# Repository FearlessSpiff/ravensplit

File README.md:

# ravensplit

(MX) Low profile split version of the raveniung

### First time setup

* Install ergogen: `npm install -g ergogen`
* Get footprints from ceoloide: `git clone https://github.com/ceoloide/ergogen-footprints ergogen/footprints/ceoloide`
* For case build install `npm install -g @jscad/cli`

## v0.1 for Cirque Trackpad

### Build

```bash
cd ergogen
cp config-v0.1.yaml config.yaml
ergogen .
```

or for building including the left case:

```bash
ergogen . && npx @jscad/cli@1 output/cases/LeftCase.jscad -of stla && npx @jscad/cli@1 output/cases/RightCase.jscad -of stla
```

### Notes

* mirror right case and cirque holder!

## v0.2 for Azoteq TPS65 touchpad

### Build

```bash
cd ergogen
cp config-v0.2.yaml config.yaml
ergogen .
```

or for building including the left case:

```bash
ergogen . && npx @jscad/cli@1 output/cases/LeftCase.jscad -of stla
```

### Notes

* mirror right case and cirque holder!
For 3d printed  case:
* top-foam-plate: 1mm thick, cut 15mm/s 90%
* bottom-foam-plate: 3mm thick, cut 12mm/s 90% 2 passes
* touchpad-overlay-tps43 sticker: Tenstickers brand vinyl, cut 10mm/s 80% power on a 10W laser
* touchpad-overlay-tps65 sticker: Tenstickers brand vinyl, cut 10mm/s 80% power on a 10W laser

### TODO

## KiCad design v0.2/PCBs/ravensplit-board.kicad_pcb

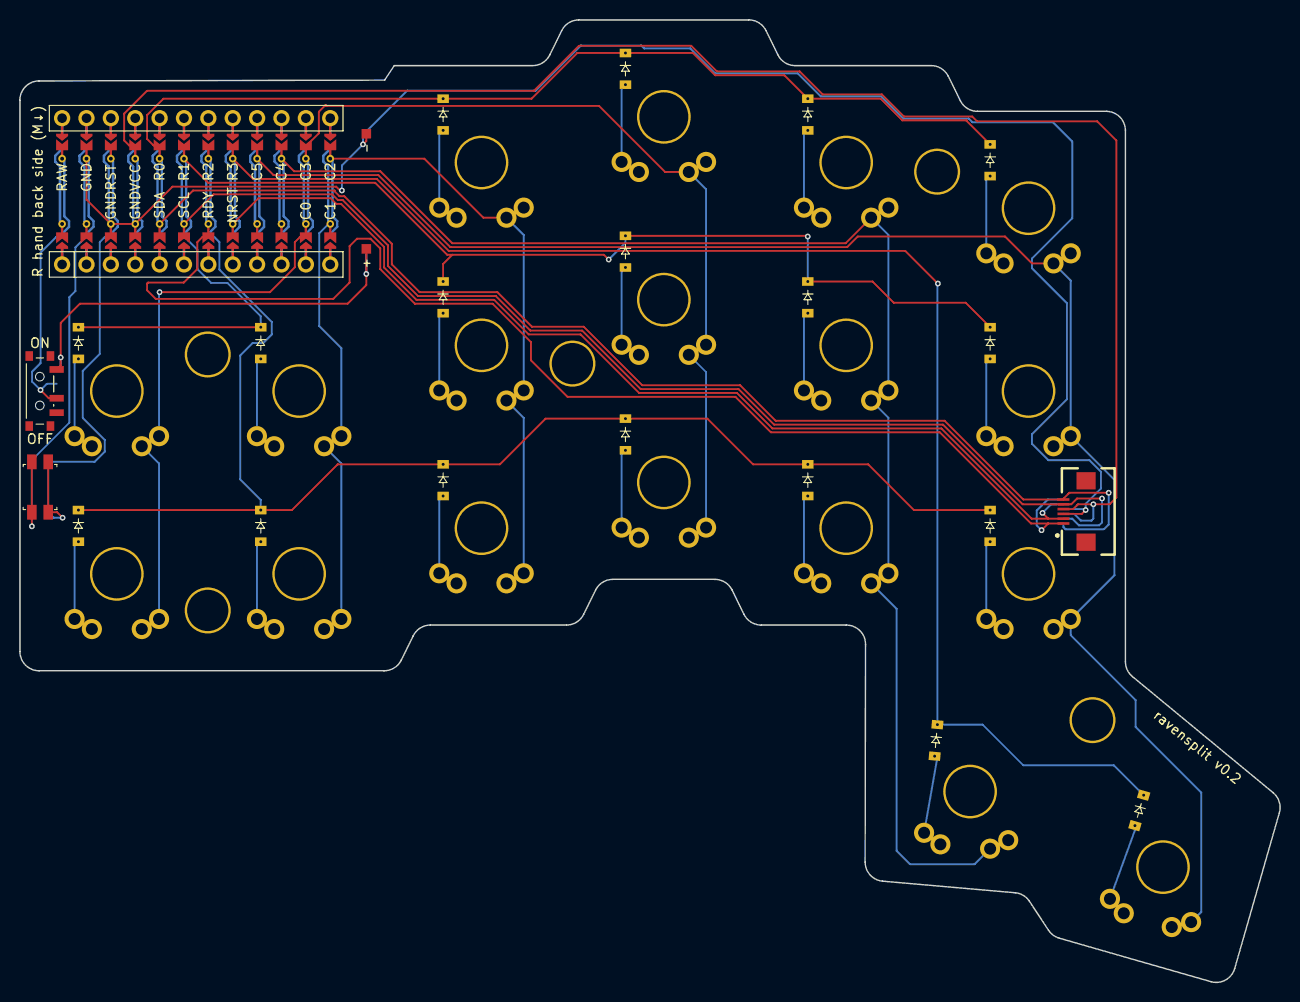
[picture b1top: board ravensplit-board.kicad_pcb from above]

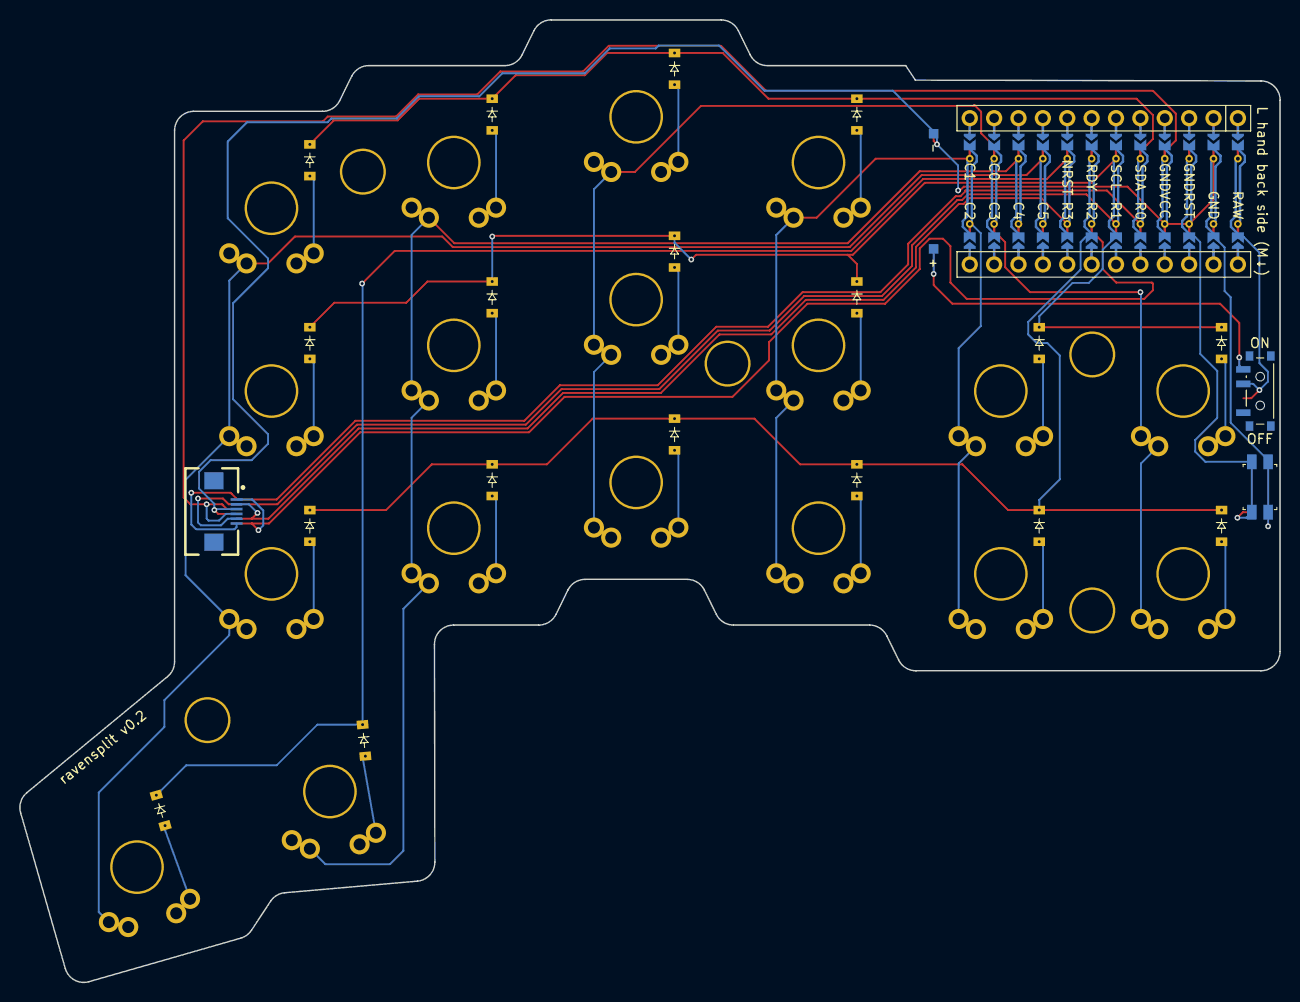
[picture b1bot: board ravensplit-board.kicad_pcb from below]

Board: 2 copper layers, 131.3 x 100.3 mm, 48 parts (19 on the bottom side), 37 nets.

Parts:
D1, D2, D3, D4, D5, D6, D7, D8, D9, D10, D11, D12, D13, D14, D15, D16, D17, D18: diode_tht_sod123
FFC1, FFC2: FPC-SMD_FPC050A004
MCU1: mcu_nice_nano
MH1, MH2, MH3, MH4, MH5: mounting_hole_npth
PAD1, PAD2: SMDPad
PWR1: power_switch_smd_side
RST1: reset_switch_smd_side
S1, S2, S3, S4, S5, S6, S7, S8, S9, S10, S11, S12, S13, S14, S15, S16, S17, S18: switch_gateron_ks27_ks33

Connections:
BAT_P: PAD1.1, PWR1.1, PWR1.3
C0: MCU1.114, S1.2, S2.2
C1: MCU1.113, S3.2, S4.2
C2: MCU1.112, S5.2, S6.2, S7.2
C3: MCU1.111, S8.2, S9.2, S10.2
C4: MCU1.110, S11.2, S12.2, S13.2, S18.2
C5: MCU1.109, S14.2, S15.2, S16.2, S17.2
GND: FFC1.3, FFC2.3, MCU1.102, MCU1.121, MCU1.122, PAD2.1, RST1.1, RST1.3
NRST: FFC1.2, FFC2.2, MCU1.117
R0: D7.1, D10.1, D13.1, D16.1, MCU1.105
R1: D2.1, D4.1, D6.1, D9.1, D12.1, D15.1, MCU1.106
R2: D1.1, D3.1, D5.1, D8.1, D11.1, D14.1, MCU1.107
R3: D17.1, D18.1, MCU1.108
RAW: MCU1.101, PWR1.2
RDY: FFC1.1, FFC2.1, MCU1.118
RST: MCU1.103, RST1.2, RST1.4
SCL: FFC1.5, FFC2.5, MCU1.119
SDA: FFC1.6, FFC2.6, MCU1.120
VCC: FFC1.4, FFC2.4, MCU1.104
index_bottom: D11.2, S11.1
index_home: D12.2, S12.1
index_top: D13.2, S13.1
inner_bottom: D14.2, S14.1
inner_home: D15.2, S15.1
inner_thumb: D17.2, S17.1
inner_top: D16.2, S16.1
middle_bottom: D8.2, S8.1
middle_home: D9.2, S9.1
middle_top: D10.2, S10.1
outer_bottom: D1.2, S1.1
outer_home: D2.2, S2.1
pinky_bottom: D3.2, S3.1
pinky_home: D4.2, S4.1
reachy_thumb: D18.2, S18.1
ring_bottom: D5.2, S5.1
ring_home: D6.2, S6.1
ring_top: D7.2, S7.1

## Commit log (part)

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2025-02-06 Add initial version
    TODO:
    - battery connector
    - mcu top cutout
    - top-plate
    - foam-plates
    - cases
2025-02-07 fix mount hole and top plate
2025-02-07 "Almost" finished ergogen PCB definition
2025-02-07 Use pads from mrzealot as the label works better reversible
2025-02-07 Remove unused mount hole
2025-02-07 Fix untested bottom foam plate
2025-02-09 Add outlines to define a case wall
2025-02-09 Add first (maybe) usable case without mounting holes yet
2025-02-10 Add standoffs to case
2025-02-10 Change to smaller footprint and tighter case tolerance
2025-02-10 Make board bigger for the MCU
2025-02-10 Add right case with cirque extension (must be mirrored before printing)
2025-02-10 Fix cirque standoff height
2025-02-11 "Final" version for the cirque holder. STL follows...
2025-02-11 Add not yet measured case cutouts for power- and reset switch
2025-02-12 Nicer case cutouts for switches
2025-02-12 Adapt pcb components to smaller footprint
2025-02-12 Remove PCB top plate label for a clean black look
2025-02-13 Fix thumb columns, easier routing for MCU, and fix label
2025-02-13 Add a maybe finished PCB for v0.1
2025-02-14 Center MCU better and auto redo PCBs
2025-02-14 Fix ugly route around diode
2025-02-14 Fix FFC connector orientation
2025-02-14 Add correct routed PCB with DRC ran
2025-02-14 Add text on both sides of PCB
2025-02-14 Fix an obvious ugly rout from auto routing
2025-02-19 Add some more KiCad stuff to .gitignore
2025-02-19 Add forgotten mirrored FFC connector
2025-02-19 Add final and ordered V0.1 PCBs and gerber files
2025-02-19 Add untested bottom foam plate
2025-02-20 Add a right and left bottom foam plate
2025-02-20 Add STLs for cases and cirque adapter
2025-02-27 Better bottom foam plate
2025-03-07 Add 35mm cirque stl
2025-03-19 Updates for v0.1
2026-03-09 Start Azoteq v2 version and fix pad in PCB
2026-03-09 PCB: Fix v0.2 text, pads and switch on/off position
2026-03-09 Add todos in readme
2026-03-09 Add draft 6pin ffc connector
2026-03-09 Integrate new fpc connector and wire it to MCU
2026-03-10 Update case to house the TPS65 touchpad
2026-03-10 Add cases for TPS65
2026-03-11 Edit 6pin FFC connector according to aliexpress image
2026-03-11 Added FPC model number and bit better pads
2026-03-12 Adapt case design to real touchpad (and printer ;-))
2026-03-14 Adapted FFC footprint to real world connector
2026-03-14 Make touchpad also reversible
2026-03-14 Fix power switch behavior as the default has changed meanwhile. Would be better to pin a tag on ceoloid footprints...
2026-03-16 Nicer PCB label
2026-03-16 Fix FFC pin order and add assembly hints
2026-03-17 Fix FFC name
2026-03-17 Add build for both cases
2026-03-17 Add maybe final stuff for 0.2 before PCB design
2026-03-17 Add routed PCBs and Gerbers
2026-03-23 Add printable KLP Lame Bambustudio projects
2026-03-23 Add foam plate info
2026-03-23 Add gcode for top and bottom plate (CR-Falcon Laser)
2026-04-02 Add cutout for power wire for bigger battery placed under touchpad
2026-04-19 Add a case with holes to be used with 6mm M2 standoffs and 3mm long M2 screws
2026-04-22 Add new cases for standoffs and integrated threads
2026-06-11 Add low profile case
2026-06-16 added new cases
2026-06-20 Add stuff to be able to use a sticker overlay
